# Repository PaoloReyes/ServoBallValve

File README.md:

# ServoBallValve

## Overview
This repository contains the code and design (PCB) for the Angled Controlled valve (ServoBallValve) module, which serves as an actuator for dispensing paint in the automatic paint machine. The ServoBallValve is responsible for controlling the flow of paint according to the desired angle.

## Hardware

## Features
- **Positional Control**: Uses a motor in a closed loop system to precisely control the angle of the valve.
- **Flow Regulation**: Regulates the paint flow rate based on the angle setpoint.
- **Sensor Integration**: Utilizes High resolution Potentiometer for position feedback and validation.

## Communication Protocol
The ServoBallValve module receives and sends commands via a predefined protocol:
- `50Hz Signal` - It is the wave carrier for the data.
- `MicroSeconds codification` - The data is codified in the pulse width of the signal by sending a high pulse in the range of 1000 to 2000 microseconds.

## Troubleshooting
| Issue               | Possible Cause                | Solution |
|---------------------|-----------------------------|----------|
| Incorrect positioning| Calibration error           | Re-run calibration sequence |
| No response       | Communication failure       | Verify communication wiring and settings |
| Erratic flow        | Sensor malfunction or misalignment| Check sensor connections and alignment |

## Contributors
- **Paolo Reyes** - Lead Developer

## License
This project is licensed under the MIT License - see the LICENSE file for details.

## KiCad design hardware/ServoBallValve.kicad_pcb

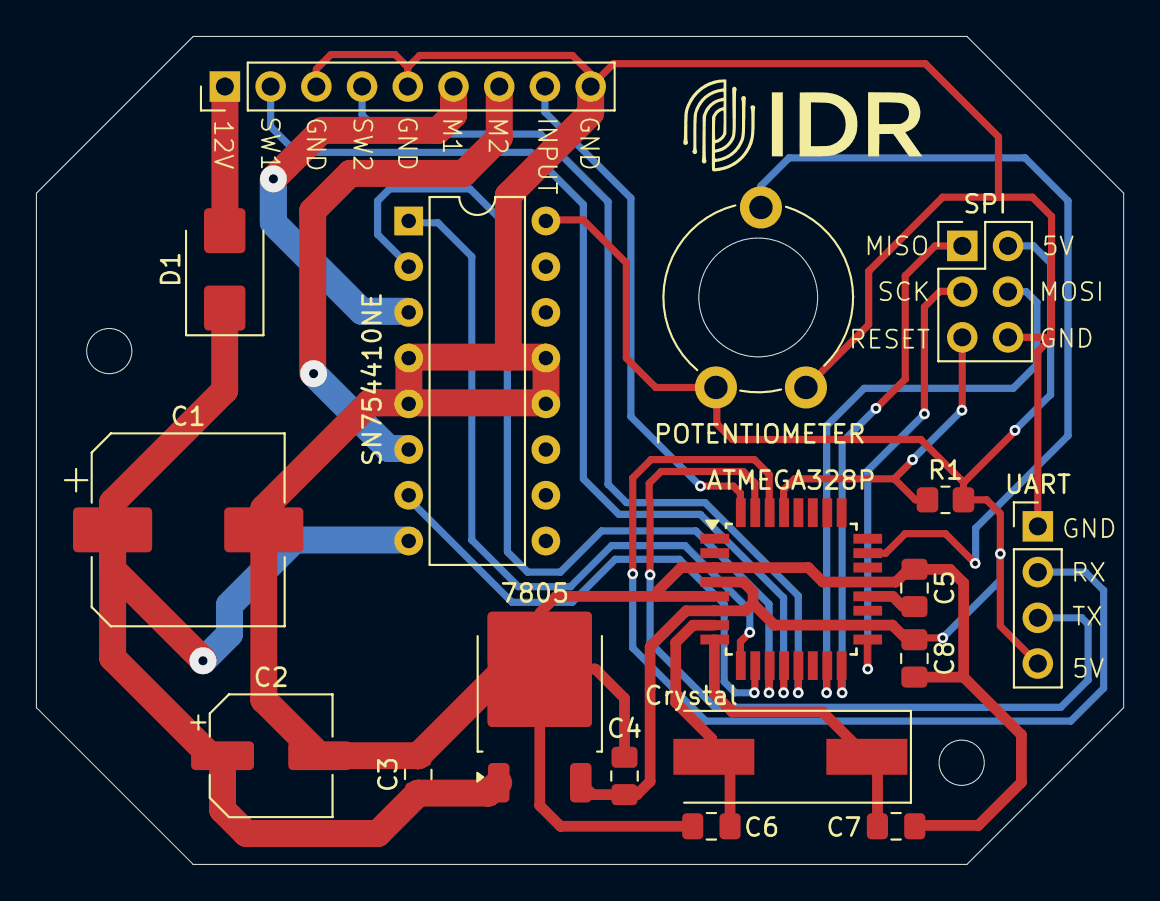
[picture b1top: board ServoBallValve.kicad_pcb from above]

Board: 2 copper layers, 60.4 x 46.0 mm, 18 parts (0 on the bottom side), 22 nets.

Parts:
7805: L7805; TO-252-2
ATMEGA328P: ATmega328P-A; TQFP-32_7x7mm_P0.8mm
C1: Capacitor 220uf; CP_Elec_10x10.5
C2: Capacitor 100uf; CP_Elec_6.3x7.7
C3: Capacitor 4.7uf; C_0805_2012Metric_Pad1.18x1.45mm_HandSolder
C4: Capacitor 2.2uf; C_0805_2012Metric_Pad1.18x1.45mm_HandSolder
C5, C8: Capacitor 100nf; C_0805_2012Metric_Pad1.18x1.45mm_HandSolder
C6, C7: Capacitor 22pf; C_0805_2012Metric_Pad1.18x1.45mm_HandSolder
Crystal: 16MHzCrystal; Crystal_SMD_HC49-SD
D1: US2AA; D_SMB
J3: Conn_01x09_Socket; PinHeader_1x09_P2.54mm_Vertical
POTENTIOMETER: R_Potentiometer; Potentiometer_Piher_PT-10-V10_Vertical_Hole
R1: Resistor 1K; R_0805_2012Metric_Pad1.20x1.40mm_HandSolder
SN754410NE: L293D; DIP-16_W7.62mm
SPI: Conn_02x03_Counter_Clockwise; PinHeader_2x03_P2.54mm_Vertical
UART: Conn_01x04_Socket; PinHeader_1x04_P2.54mm_Vertical

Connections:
5V: 7805.3 (OUT), ATMEGA328P.4 (VCC), ATMEGA328P.6 (VCC), ATMEGA328P.18 (AVCC), C4.1, C8.1, POTENTIOMETER.3, R1.2, SN754410NE.16 (VCC1), SPI.2, UART.4
24V: 7805.1 (IN), C1.1, C2.1, C3.1, D1.1 (K), SN754410NE.8 (VCC2)
24VINPUT: D1.2 (A), J3.1
ENA: ATMEGA328P.9 (PD5), SN754410NE.1 (EN1,2)
GND: 7805.2 (GND), ATMEGA328P.3 (GND), ATMEGA328P.5 (GND), ATMEGA328P.21 (GND), C1.2, C2.2, C3.2, C4.2, C5.1, C6.2, C7.2, C8.2, J3.3, J3.5, J3.9, POTENTIOMETER.1, SN754410NE.4 (GND), SN754410NE.5 (GND), SN754410NE.12 (GND), SN754410NE.13 (GND), SPI.6, UART.1
IN1: ATMEGA328P.11 (PD7), SN754410NE.2 (1A)
IN2: ATMEGA328P.10 (PD6), SN754410NE.7 (2A)
M1: J3.6, SN754410NE.3 (1Y)
M2: J3.7, SN754410NE.6 (2Y)
MISO: ATMEGA328P.16 (PB4), SPI.1
MOSI: ATMEGA328P.15 (PB3), SPI.4
unnamed: ATMEGA328P.20 (AREF), C5.2
unnamed: ATMEGA328P.23 (PC0), POTENTIOMETER.2
unnamed: ATMEGA328P.7 (XTAL1/PB6), C6.1, Crystal.2
unnamed: ATMEGA328P.8 (XTAL2/PB7), C7.1, Crystal.1
RESET: ATMEGA328P.29 (~RESET/PC6), R1.1, SPI.5
RX: ATMEGA328P.30 (PD0), UART.2
S1.1: ATMEGA328P.12 (PB0), J3.2
S2.1: ATMEGA328P.13 (PB1), J3.4
SCK: ATMEGA328P.17 (PB5), SPI.3
Signal: ATMEGA328P.32 (PD2), J3.8
TX: ATMEGA328P.31 (PD1), UART.3

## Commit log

2025-02-13 feat(ServoBallValve): Hardware and Software Release
2025-02-15 idr 15/02
2025-02-17 feat(ServoBallValve): Hardware and Software Release for 3/4 valve with first software corrected for mechanical issues
2025-02-17 feat(README): Added readme
2025-03-26 fix(readme): updated image
2025-04-16 Update: April 2025 update
